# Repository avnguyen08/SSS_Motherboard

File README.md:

# SCR Controller – R&D Project
Precise gate control system for 6 high-power SCR channels using a Microcontroller PWM with opto-isolated trigger circuit.

## Overview
This project develops a programmable gate pulse controller for SCRs used in magnetic particle inspection (MPI) machines. It provides isolated, high-current gate pulses using an isolated PWM, low pass filter, and power op-amp stage, enabling safe, flexible SCR firing control.

Applications:
- Non-destructive testing
- High-current industrial power stages

## Key Features
- PWM-based gate pulse generation (10–80 µs pulse width)
- Up to 10V and 1000 mA opto-isolated gate driver
- Configurable pulse width and delay
- LCD Diagnostics Display
- Powered from 240V - 480V DC Range

## Getting Started

### Hardware Setup
- Connect board's 6 SCR channels to respective gate and anode
- Connect energize button and input signal
- Connect to 240V - 480V power source

### Firmware Notes
- `main.c` sets up SPI and gate pulse logic
- Pulse parameters are hardcoded for now (change in `config.h`)

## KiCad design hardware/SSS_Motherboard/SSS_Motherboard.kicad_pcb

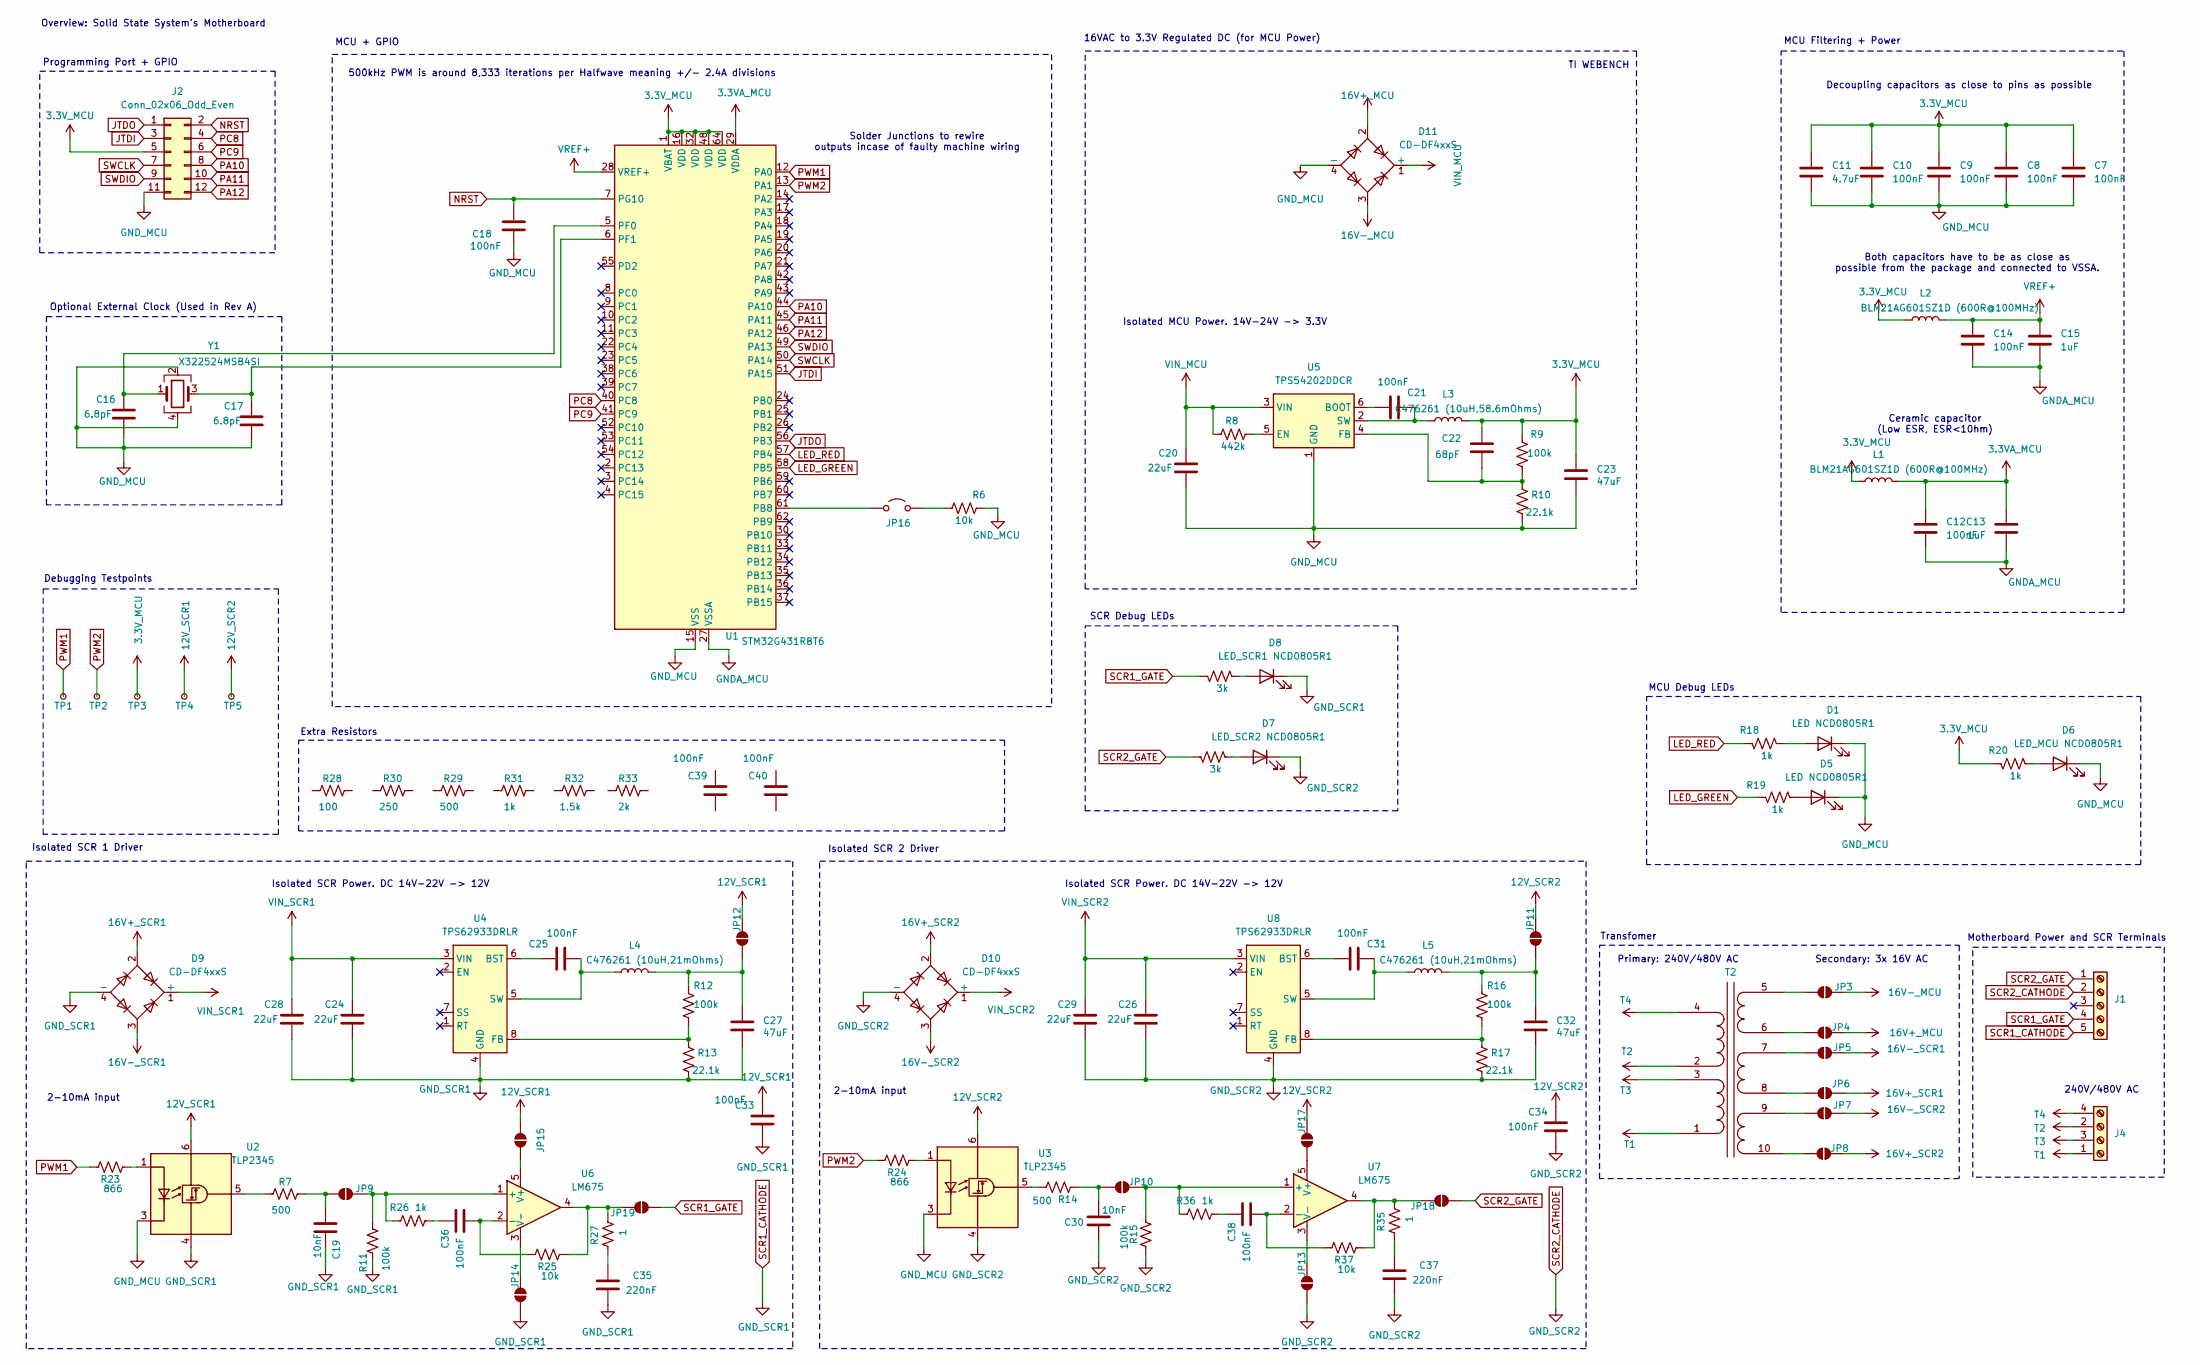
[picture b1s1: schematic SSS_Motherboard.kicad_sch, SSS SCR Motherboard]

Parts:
C7, C8, C9, C10, C12, C14, C18, C21, C25, C31, C33, C34, C36, C38, C39, C40: 100nF; C_0805_2012Metric
C11: 4.7uF; C_0805_2012Metric
C13, C15: 1uF; C_0805_2012Metric
C16, C17: 6.8pF; C_0805_2012Metric
C19, C30: 10nF; C_0805_2012Metric
C20, C24, C26, C28, C29: 22uF; C_0805_2012Metric
C22: 68pF; C_0805_2012Metric
C23, C27, C32: 47uF; C_0805_2012Metric
C35, C37: 220nF; C_0805_2012Metric
D1, D5: LED NCD0805R1; D_0805_2012Metric
D6: LED_MCU NCD0805R1; D_0805_2012Metric
D7: LED_SCR2 NCD0805R1; D_0805_2012Metric
D8: LED_SCR1 NCD0805R1; D_0805_2012Metric
D9, D10, D11: CD-DF4xxS; CD-DF4xxS(L)
J1: Screw_Terminal_01x05; 5_Connector_11.13_Pitch
J2: Conn_02x06_Odd_Even; PinHeader_2x06_P2.54mm_Vertical
J4: Screw_Terminal_01x04; 4_Connector_11.13_Pitch
JP3, JP4, JP5, JP6, JP7, JP8, JP9, JP10, JP11, JP12, JP13, JP14, JP15, JP17, JP18, JP19: SolderJumper_2_Open; SolderJumper-2_P1.3mm_Open_Pad1.0x1.5mm
JP16: Jumper_2_Open; PinHeader_1x02_P2.54mm_Vertical
L1, L2: BLM21AG601SZ1D (600R@100MHz); L_0805_2012Metric
L3: C476261 (10uH,58.6mOhms); SRN6045
L4, L5: C476261 (10uH,21mOhms); SRN6045
R6, R25, R37: 10k; R_0805_2012Metric
R7, R14, R29: 500; R_0805_2012Metric
R8: 442k; R_0805_2012Metric
R9, R11, R12, R15, R16: 100k; R_0805_2012Metric
R10, R13, R17: 22.1k; R_0805_2012Metric
R18, R19, R20, R26, R31, R36: 1k; R_0805_2012Metric
R21, R22: 3k; R_0805_2012Metric
R23, R24: 866; R_0805_2012Metric
R27, R35: 1; R_0805_2012Metric
R28: 100; R_0805_2012Metric
R30: 250; R_0805_2012Metric
R32: 1.5k; R_0805_2012Metric
R33: 2k; R_0805_2012Metric
T2: Transformer_2P_3S; Transformer
TP1, TP2, TP3, TP4, TP5: TestPoint_Small; TestPoint_Loop_D2.50mm_Drill1.0mm
U1: STM32G431RBT6; LQFP-64_10x10mm_P0.5mm
U2, U3: TLP2345; SO-5-6_4.55x3.7mm_P1.27mm
U4, U8: TPS62933DRLR; SOT-583-8
U5: TPS54202DDCR; SOT-23-6
U6, U7: LM675; TO-220-5_P3.4x3.7mm_StaggerOdd_Lead3.8mm_Vertical
Y1: X322524MSB4SI; Crystal_SMD_3225-4Pin_3.2x2.5mm

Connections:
3.3VA_MCU: C12.1, C13.1, L1.1, U1.29 (VDDA)
3.3V_MCU: C7.1, C8.1, C9.1, C10.1, C11.1, C22.2, C23.1, J2.5, L1.2, L2.1, L3.1, R9.1, R20.1, TP3.1, U1.1 (VBAT), U1.16 (VDD), U1.32 (VDD), U1.48 (VDD), U1.64 (VDD)
12V_SCR1: C33.1, JP12.2 (B), JP15.2 (B), TP4.1, U2.6 (VDD)
12V_SCR2: C34.1, JP11.2 (B), JP17.2 (B), TP5.1, U3.6 (VDD)
16V+_MCU: D11.2, JP4.2 (B)
16V+_SCR1: D9.2, JP6.2 (B)
16V+_SCR2: D10.2, JP8.2 (B)
16V-_MCU: D11.3, JP3.2 (B)
16V-_SCR1: D9.3, JP5.2 (B)
16V-_SCR2: D10.3, JP7.2 (B)
GNDA_MCU: C12.2, C13.2, C14.2, C15.2, U1.27 (VSSA)
GND_MCU: C7.2, C8.2, C9.2, C10.2, C11.2, C16.2, C17.2, C18.1, C20.2, C23.2, D1.1 (K), D5.1 (K), D6.1 (K), D11.4 (-), J2.11, R6.1, R10.1, U1.15 (VSS), U1.31 (VSS), U1.47 (VSS), U1.63 (VSS), U2.3 (K), U3.3 (K), U5.1 (GND), Y1.2, Y1.4
JTDI: J2.3, U1.51 (PA15)
JTDO: J2.1, U1.56 (PB3)
LED_GREEN: R19.1, U1.58 (PB5)
LED_RED: R18.1, U1.57 (PB4)
NRST: C18.2, J2.2, U1.7 (PG10)
unnamed: C35.1, R27.2
unnamed: C36.1, R26.1
unnamed: C37.1, R35.2
unnamed: C38.1, R36.1
unnamed: D1.2 (A), R18.2
unnamed: D5.2 (A), R19.2
unnamed: D6.2 (A), R20.2
unnamed: D7.2 (A), R21.2
unnamed: D8.2 (A), R22.2
unnamed: JP3.1 (A), T2.5 (SA)
unnamed: JP4.1 (A), T2.6 (SB)
unnamed: JP5.1 (A), T2.7 (SC)
unnamed: JP6.1 (A), T2.8 (SD)
unnamed: JP7.1 (A), T2.9 (SC)
unnamed: JP8.1 (A), T2.10 (SD)
unnamed: C19.1, JP9.1 (A), R7.2
unnamed: JP9.2 (B), R11.2, R26.2, U6.1 (+)
unnamed: C30.1, JP10.1 (A), R14.2
unnamed: JP10.2 (B), R15.2, R36.2, U7.1 (+)
unnamed: C32.1, JP11.1 (A), L5.1, R16.1
unnamed: C27.1, JP12.1 (A), L4.1, R12.1
unnamed: JP13.2 (B), U7.3 (V-)
unnamed: JP14.2 (B), U6.3 (V-)
unnamed: JP15.1 (A), U6.5 (V+)
unnamed: JP16.1 (A), U1.61 (PB8)
unnamed: JP16.2 (B), R6.2
unnamed: JP17.1 (A), U7.5 (V+)
unnamed: JP18.2 (B), R35.1, R37.1, U7.4
unnamed: JP19.2 (B), R25.1, R27.1, U6.4
unnamed: C16.1, U1.5 (PF0), Y1.1
unnamed: C17.1, U1.6 (PF1), Y1.3
unnamed: R23.1, U2.1 (A)
unnamed: R7.1, U2.5 (VO)
unnamed: R24.1, U3.1 (A)
unnamed: R14.1, U3.5 (VO)
unnamed: C25.1, U4.6 (BST)
unnamed: R12.2, R13.2, U4.8 (FB)
unnamed: C25.2, L4.2, U4.5 (SW)
unnamed: C21.2, U5.6 (BOOT)
unnamed: R8.1, U5.5 (EN)
unnamed: C22.1, R9.2, R10.2, U5.4 (FB)
unnamed: C21.1, L3.2, U5.2 (SW)
unnamed: C36.2, R25.2, U6.2 (-)
unnamed: C38.2, R37.2, U7.2 (-)
unnamed: C31.2, U8.6 (BST)
unnamed: R16.2, R17.2, U8.8 (FB)
unnamed: C31.1, L5.2, U8.5 (SW)
PA10: J2.8, U1.44 (PA10)
PA11: J2.10, U1.45 (PA11)
PA12: J2.12, U1.46 (PA12)
PC8: J2.4, U1.40 (PC8)
PC9: J2.6, U1.41 (PC9)
PWM1: R23.2, TP1.1, U1.12 (PA0)
PWM2: R24.2, TP2.1, U1.13 (PA1)
SCR1_CATHODE: C19.2, C24.2, C27.2, C28.2, C33.2, C35.2, D8.1 (K), D9.4 (-), J1.5, JP14.1 (A), R11.1, R13.1, U2.4 (GND), U4.4 (GND)
SCR1_GATE: J1.4, JP19.1 (A), R22.1
SCR2_CATHODE: C26.2, C29.2, C30.2, C32.2, C34.2, C37.2, D7.1 (K), D10.4 (-), J1.2, JP13.1 (A), R15.1, R17.1, U3.4 (GND), U8.4 (GND)
SCR2_GATE: J1.1, JP18.1 (A), R21.1
SWCLK: J2.7, U1.50 (PA14)
SWDIO: J2.9, U1.49 (PA13)
T1: J4.1 (Pin_4), T2.1 (AA)
T2: J4.2, T2.2 (AA)
T3: J4.3, T2.3 (AB)
T4: J4.4 (Pin_1), T2.4 (AB)
VIN_MCU: C20.1, D11.1 (+), R8.2, U5.3 (VIN)
VIN_SCR1: C24.1, C28.1, D9.1 (+), U4.3 (VIN)
VIN_SCR2: C26.1, C29.1, D10.1 (+), U8.3 (VIN)
VREF+: C14.1, C15.1, L2.2, U1.28 (VREF+)

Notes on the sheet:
Secondary: 3x 16V AC
Isolated SCR Power. DC 14V-22V -> 12V
Motherboard Power and SCR Terminals
Isolated SCR 2 Driver
MCU + GPIO
Isolated SCR 1 Driver
Decoupling capacitors as close to pins as possible
Primary: 240V/480V AC
Optional External Clock (Used in Rev A)
Transfomer
SCR Debug LEDs
2-10mA input
Solder Junctions to rewire outputs incase of faulty machine wiring
Debugging Testpoints
500kHz PWM is around 8,333 iterations per Halfwave meaning +/- 2.4A divisions
MCU Filtering + Power
Isolated MCU Power. 14V-24V -> 3.3V
Both capacitors have to be as close as possible from the package and connected to VSSA.
TI WEBENCH
Ceramic capacitor (Low ESR, ESR<10hm)
Extra Resistors
Programming Port + GPIO
MCU Debug LEDs
240V/480V AC
Overview: Solid State System's Motherboard
16VAC to 3.3V Regulated DC (for MCU Power)

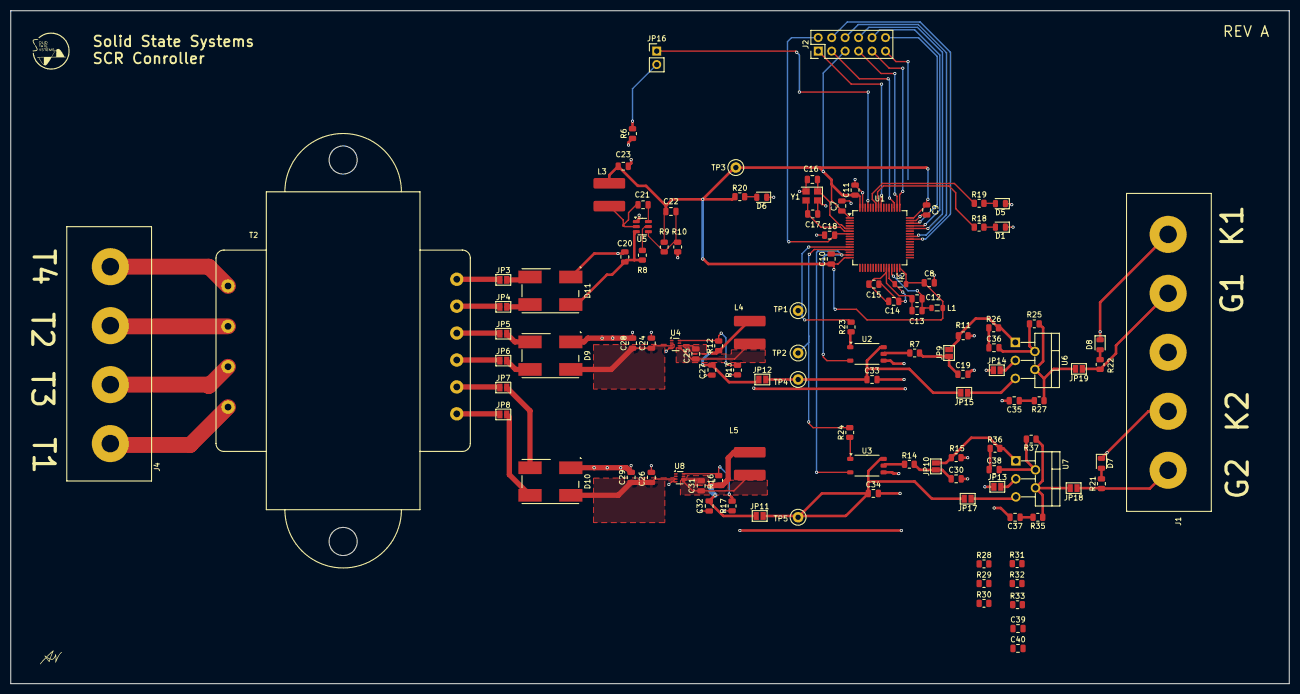
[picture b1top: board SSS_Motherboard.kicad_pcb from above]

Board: 2 copper layers, 241.3 x 127.0 mm, 113 parts (0 on the bottom side), 85 nets.

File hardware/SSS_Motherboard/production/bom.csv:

Designator,Footprint,Quantity,Value,LCSC Part #
"C10, C12, C14, C18, C21, C25, C31, C33, C34, C36, C38, C39, C40, C7, C8, C9",0805,16,100nF,
C11,0805,1,4.7uF,
"C13, C15",0805,2,1uF,
"C16, C17",0805,2,6.8pF,
"C19, C30",0805,2,10nF,
"C20, C24, C26, C28, C29",0805,5,22uF,
C22,0805,1,68pF,
"C23, C27, C32",0805,3,47uF,
"C35, C37",0805,2,220nF,
"D1, D5",0805,2,LED   NCD0805R1,
"D10, D11, D9",CD-DF4xxS(L),3,CD-DF4xxS,
D6,0805,1,LED_MCU   NCD0805R1,
D7,0805,1,LED_SCR2   NCD0805R1,
D8,0805,1,LED_SCR1   NCD0805R1,
J1,5_Connector_11.13_Pitch,1,Screw_Terminal_01x05,
J2,PinHeader_2x06_P2.54mm_Vertical,1,Conn_02x06_Odd_Even,
J4,4_Connector_11.13_Pitch,1,Screw_Terminal_01x04,
JP16,PinHeader_1x02_P2.54mm_Vertical,1,Jumper_2_Open,
"L1, L2",0805,2,BLM21AG601SZ1D (600R@100MHz),
L3,SRN6045,1,"C476261 (10uH,58.6mOhms)",
"L4, L5",SRN6045,2,"C476261 (10uH,21mOhms)",
"R10, R13, R17",0805,3,22.1k,
"R11, R12, R15, R16, R9",0805,5,100k,
"R14, R29, R7",0805,3,500,
"R18, R19, R20, R26, R31, R36",0805,6,1k,
"R21, R22",0805,2,3k,
"R23, R24",0805,2,866,
"R25, R37, R6",0805,3,10k,
"R27, R35",0805,2,1,
R28,0805,1,100,
R30,0805,1,250,
R32,0805,1,1.5k,
R33,0805,1,2k,
R8,0805,1,442k,
T2,Transformer,1,Transformer_2P_3S,
"TP1, TP2, TP3, TP4, TP5",TestPoint_Loop_D2.50mm_Drill1.0mm,5,TestPoint_Small,
U1,LQFP-64_10x10mm_P0.5mm,1,STM32G431RBT6,
"U2, U3",SO-5-6_4.55x3.7mm_P1.27mm,2,TLP2345,
"U4, U8",SOT-583-8,2,TPS62933DRLR,
U5,SOT-23-6,1,TPS54202DDCR,
"U6, U7",TO-220-5_P3.4x3.7mm_StaggerOdd_Lead3.8mm_Vertical,2,LM675,
Y1,Crystal_SMD_3225-4Pin_3.2x2.5mm,1,X322524MSB4SI,

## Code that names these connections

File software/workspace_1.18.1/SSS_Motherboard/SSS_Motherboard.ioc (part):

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Mcu.Name=STM32G431R(6-8-B)Tx
Mcu.Package=LQFP64
Mcu.UserName=STM32G431RBTx
PA0.Signal=S_TIM2_CH1
PA1.Signal=S_TIM2_CH2
PB4.GPIOParameters=PinState,GPIO_PuPd,GPIO_Label
PB4.GPIO_Label=LED_RED
PB4.GPIO_PuPd=GPIO_NOPULL
PB4.PinState=GPIO_PIN_SET
PB4.Signal=GPIO_Output
PB5.GPIOParameters=PinState,GPIO_Label
PB5.GPIO_Label=LED_GREEN
PB5.PinState=GPIO_PIN_SET
PB5.Signal=GPIO_Output
PF0-OSC_IN.Mode=HSE-External-Oscillator
PF0-OSC_IN.Signal=RCC_OSC_IN
PF1-OSC_OUT.Mode=HSE-External-Oscillator
PF1-OSC_OUT.Signal=RCC_OSC_OUT
RCC.HSE_VALUE=24000000
RCC.SYSCLKFreq_VALUE=16000000
board=custom

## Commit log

2025-05-31 Mother board project git start
2025-07-15 approved schematic
2025-09-15 manufacturing batch
2025-09-29 added software files
